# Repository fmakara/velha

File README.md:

# velha
Jogo da velha para o Mural do PET

Feito com KiCAD versão 4.0.2 e Atmel Studio

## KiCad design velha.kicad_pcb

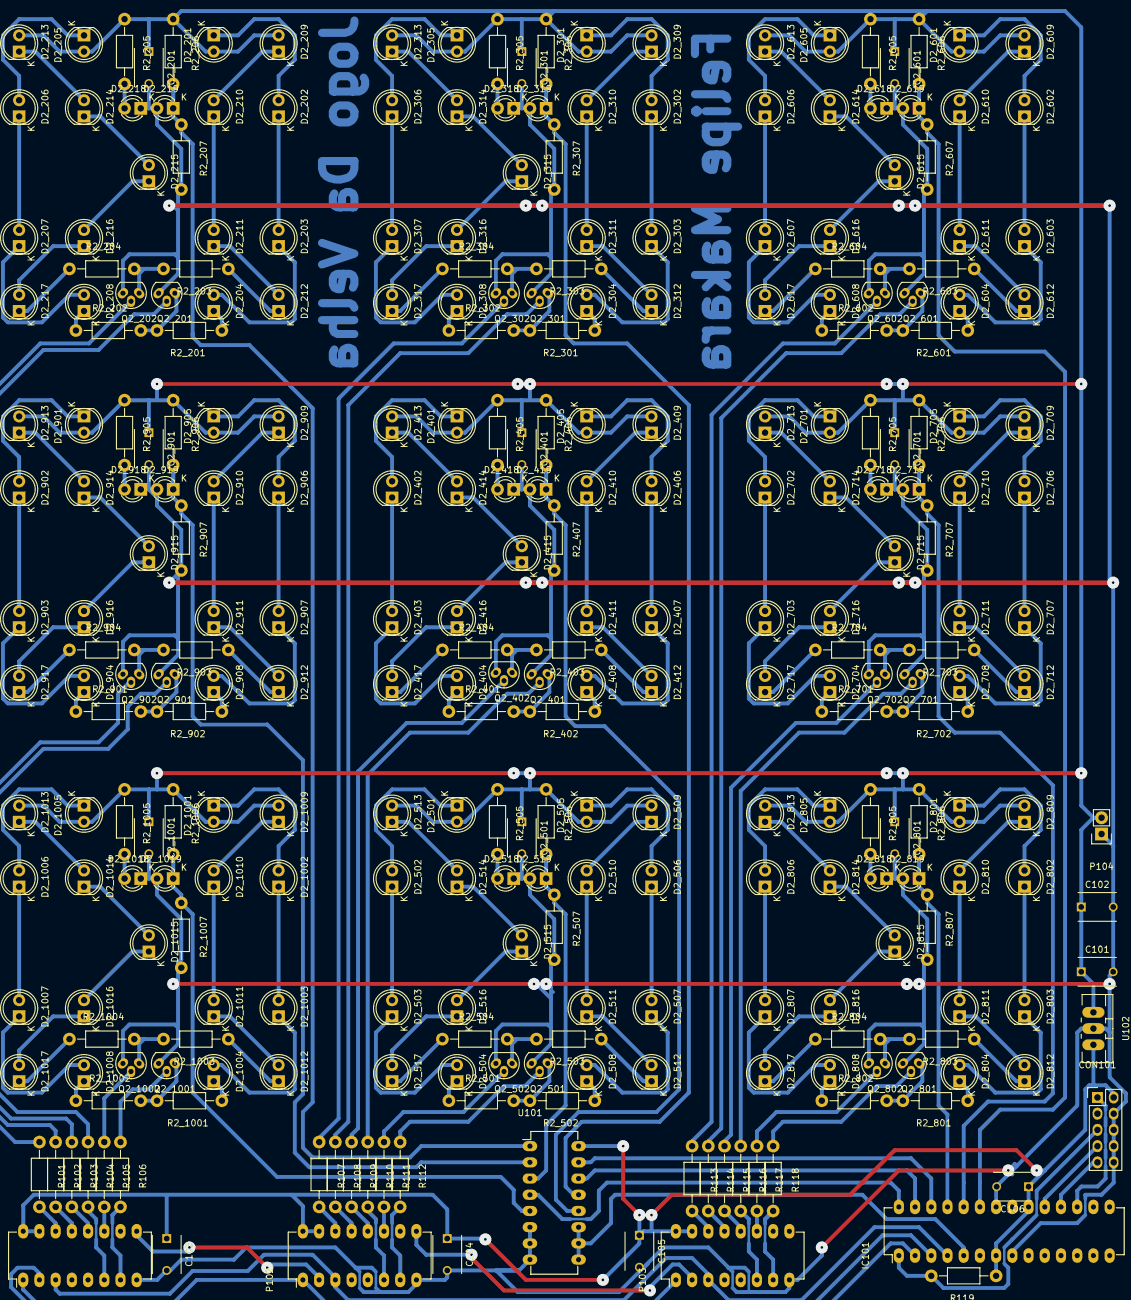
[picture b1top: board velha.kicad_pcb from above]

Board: 2 copper layers, 294 parts (0 on the bottom side), 241 nets.

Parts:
C2_201, C2_301, C2_401, C2_501, C2_601, C2_701, C2_801, C2_901, C2_1001, C102, C103, C104, C105, C106: 100n; C_Disc_D6_P5
C101: 100u; C_Disc_D6_P5
CON101: AVR-ISP-10; Pin_Header_Straight_2x05
D2_201, D2_202, D2_203, D2_204, D2_205, D2_206, D2_207, D2_208, D2_301, D2_302, D2_303, D2_304, D2_305, D2_306, D2_307, D2_308, D2_401, D2_402, D2_403, D2_404, D2_405, D2_406, D2_407, D2_408, D2_501, D2_502, D2_503, D2_504, D2_505, D2_506, D2_507, D2_508, D2_601, D2_602, D2_603, D2_604, D2_605, D2_606, D2_607, D2_608, D2_701, D2_702, D2_703, D2_704, D2_705, D2_706, D2_707, D2_708, D2_801, D2_802, D2_803, D2_804, D2_805, D2_806, D2_807, D2_808, D2_901, D2_902, D2_903, D2_904, D2_905, D2_906, D2_907, D2_908, D2_1001, D2_1002, D2_1003, D2_1004, D2_1005, D2_1006, D2_1007, D2_1008: G; LED-5MM
D2_209, D2_210, D2_211, D2_212, D2_213, D2_214, D2_215, D2_216, D2_217, D2_309, D2_310, D2_311, D2_312, D2_313, D2_314, D2_315, D2_316, D2_317, D2_409, D2_410, D2_411, D2_412, D2_413, D2_414, D2_415, D2_416, D2_417, D2_509, D2_510, D2_511, D2_512, D2_513, D2_514, D2_515, D2_516, D2_517, D2_609, D2_610, D2_611, D2_612, D2_613, D2_614, D2_615, D2_616, D2_617, D2_709, D2_710, D2_711, D2_712, D2_713, D2_714, D2_715, D2_716, D2_717, D2_809, D2_810, D2_811, D2_812, D2_813, D2_814, D2_815, D2_816, D2_817, D2_909, D2_910, D2_911, D2_912, D2_913, D2_914, D2_915, D2_916, D2_917, D2_1009, D2_1010, D2_1011, D2_1012, D2_1013, D2_1014, D2_1015, D2_1016, D2_1017: R; LED-5MM
D2_218, D2_318, D2_418, D2_518, D2_618, D2_718, D2_818, D2_918, D2_1018: LED; LED-3MM
D2_219, D2_319, D2_419, D2_519, D2_619, D2_719, D2_819, D2_919, D2_1019: PHOTO; LED-3MM
IC101: ATMEGA328P-P; DIP-28_W7.62mm_LongPads
P101, P102, P103: 4094; DIP-16_W7.62mm_LongPads
P104: CONN_01X02; Pin_Header_Straight_1x02
Q2_201, Q2_202, Q2_301, Q2_302, Q2_401, Q2_402, Q2_501, Q2_502, Q2_601, Q2_602, Q2_701, Q2_702, Q2_801, Q2_802, Q2_901, Q2_902, Q2_1001, Q2_1002: Q_NPN_CBE; TO-92_Molded_Narrow_Oval
R2_201, R2_202, R2_203, R2_301, R2_302, R2_303, R2_401, R2_402, R2_403, R2_501, R2_502, R2_503, R2_601, R2_602, R2_603, R2_701, R2_702, R2_703, R2_801, R2_802, R2_803, R2_901, R2_902, R2_903, R2_1001, R2_1002, R2_1003: 100r; Resistor_Horizontal_RM10mm
R2_204, R2_304, R2_404, R2_504, R2_604, R2_704, R2_804, R2_904, R2_1004: 50r; Resistor_Horizontal_RM10mm
R2_205, R2_305, R2_405, R2_505, R2_605, R2_705, R2_805, R2_905, R2_1005: 1k; Resistor_Horizontal_RM10mm
R2_206, R2_207, R2_306, R2_307, R2_406, R2_407, R2_506, R2_507, R2_606, R2_607, R2_706, R2_707, R2_806, R2_807, R2_906, R2_907, R2_1006, R2_1007, R119: 10k; Resistor_Horizontal_RM10mm
R101, R102, R103, R104, R105, R106, R107, R108, R109, R110, R111, R112, R113, R114, R115, R116, R117, R118: 500; Resistor_Horizontal_RM10mm
U101: 4053; DIP-16_W7.62mm_LongPads
U102: 7805; TO-220_Neutral123_Vertical_LargePads

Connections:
+5V: C103.1, C104.1, C105.1, C106.1, CON101.2, IC101.7, IC101.20, P101.15, P101.16, P102.15, P102.16, P103.15, P103.16, R119.1, U101.16
+12V: C2_201.1, C2_301.1, C2_401.1, C2_501.1, C2_601.1, C2_701.1, C2_801.1, C2_901.1, C2_1001.1, C101.1, C102.1, D2_201.2, D2_205.2, D2_209.2, D2_213.2, D2_301.2, D2_305.2, D2_309.2, D2_313.2, D2_401.2, D2_405.2, D2_409.2, D2_413.2, D2_501.2, D2_505.2, D2_509.2, D2_513.2, D2_601.2, D2_605.2, D2_609.2, D2_613.2, D2_701.2, D2_705.2, D2_709.2, D2_713.2, D2_801.2, D2_805.2, D2_809.2, D2_813.2, D2_901.2, D2_905.2, D2_909.2, D2_913.2, D2_1001.2, D2_1005.2, D2_1009.2, D2_1013.2, P104.2, R2_205.1, R2_206.1, R2_305.1, R2_306.1, R2_405.1, R2_406.1, R2_505.1, R2_506.1, R2_605.1, R2_606.1, R2_705.1, R2_706.1, R2_805.1, R2_806.1, R2_905.1, R2_906.1, R2_1005.1, R2_1006.1
/leds1/o: Q2_201.2, R102.1
/leds1/s: D2_219.1, R2_206.2, R2_207.1, U101.1
/leds1/x: Q2_202.2, R101.1
/leds2/o: Q2_301.2, R108.1
/leds2/s: D2_319.1, R2_306.2, R2_307.1, U101.13
/leds2/x: Q2_302.2, R107.1
/leds3/o: Q2_601.2, R114.1
/leds3/s: D2_619.1, IC101.23, R2_606.2, R2_607.1
/leds3/x: Q2_602.2, R113.1
/leds4/o: Q2_901.2, R104.1
/leds4/s: D2_919.1, R2_906.2, R2_907.1, U101.2
/leds4/x: Q2_902.2, R103.1
/leds5/o: Q2_401.2, R110.1
/leds5/s: D2_419.1, R2_406.2, R2_407.1, U101.12
/leds5/x: Q2_402.2, R109.1
/leds6/o: Q2_701.2, R116.1
/leds6/s: D2_719.1, IC101.24, R2_706.2, R2_707.1
/leds6/x: Q2_702.2, R115.1
/leds7/o: Q2_1001.2, R106.1
/leds7/s: D2_1019.1, R2_1006.2, R2_1007.1, U101.5
/leds7/x: Q2_1002.2, R105.1
/leds8/o: Q2_501.2, R112.1
/leds8/s: D2_519.1, R2_506.2, R2_507.1, U101.3
/leds8/x: Q2_502.2, R111.1
/leds9/o: Q2_801.2, R118.1
/leds9/s: D2_819.1, IC101.25, R2_806.2, R2_807.1
/leds9/x: Q2_802.2, R117.1
GND: C2_201.2, C2_301.2, C2_401.2, C2_501.2, C2_601.2, C2_701.2, C2_801.2, C2_901.2, C2_1001.2, C101.2, C102.2, C103.2, C104.2, C105.2, C106.2, CON101.4, CON101.6, CON101.8, CON101.10, D2_218.1, D2_219.2, D2_318.1, D2_319.2, D2_418.1, D2_419.2, D2_518.1, D2_519.2, D2_618.1, D2_619.2, D2_718.1, D2_719.2, D2_818.1, D2_819.2, D2_918.1, D2_919.2, D2_1018.1, D2_1019.2, IC101.8, IC101.22, P101.8, P102.8, P103.8, P104.1, Q2_201.3, Q2_202.3, Q2_301.3, Q2_302.3, Q2_401.3, Q2_402.3, Q2_501.3, Q2_502.3, Q2_601.3, Q2_602.3, Q2_701.3, Q2_702.3, Q2_801.3, Q2_802.3, Q2_901.3, Q2_902.3, Q2_1001.3, Q2_1002.3, R2_207.2, R2_307.2, R2_407.2, R2_507.2, R2_607.2, R2_707.2, R2_807.2, R2_907.2, R2_1007.2, U101.6, U101.7, U101.8
unnamed: CON101.1, IC101.17
unnamed: CON101.5, IC101.1, R119.2
unnamed: CON101.7, IC101.19
unnamed: CON101.9, IC101.18
unnamed: D2_201.1, D2_202.2
unnamed: D2_202.1, D2_203.2
unnamed: D2_203.1, D2_204.2
unnamed: D2_204.1, R2_201.1
unnamed: D2_205.1, D2_206.2
unnamed: D2_206.1, D2_207.2
unnamed: D2_207.1, D2_208.2
unnamed: D2_208.1, R2_202.1
unnamed: D2_209.1, D2_210.2
unnamed: D2_210.1, D2_211.2
unnamed: D2_211.1, D2_212.2
unnamed: D2_212.1, R2_203.1
unnamed: D2_213.1, D2_214.2
unnamed: D2_214.1, D2_215.2
unnamed: D2_215.1, D2_216.2
unnamed: D2_216.1, D2_217.2
unnamed: D2_217.1, R2_204.1
unnamed: D2_218.2, R2_205.2
unnamed: D2_301.1, D2_302.2
unnamed: D2_302.1, D2_303.2
unnamed: D2_303.1, D2_304.2
unnamed: D2_304.1, R2_301.1
unnamed: D2_305.1, D2_306.2
unnamed: D2_306.1, D2_307.2
unnamed: D2_307.1, D2_308.2
unnamed: D2_308.1, R2_302.1
unnamed: D2_309.1, D2_310.2
unnamed: D2_310.1, D2_311.2
unnamed: D2_311.1, D2_312.2
unnamed: D2_312.1, R2_303.1
unnamed: D2_313.1, D2_314.2
unnamed: D2_314.1, D2_315.2
unnamed: D2_315.1, D2_316.2
unnamed: D2_316.1, D2_317.2
unnamed: D2_317.1, R2_304.1
unnamed: D2_318.2, R2_305.2
unnamed: D2_401.1, D2_402.2
unnamed: D2_402.1, D2_403.2
unnamed: D2_403.1, D2_404.2
unnamed: D2_404.1, R2_401.1
unnamed: D2_405.1, D2_406.2
unnamed: D2_406.1, D2_407.2
unnamed: D2_407.1, D2_408.2
unnamed: D2_408.1, R2_402.1
unnamed: D2_409.1, D2_410.2
unnamed: D2_410.1, D2_411.2
unnamed: D2_411.1, D2_412.2
unnamed: D2_412.1, R2_403.1
unnamed: D2_413.1, D2_414.2
unnamed: D2_414.1, D2_415.2
unnamed: D2_415.1, D2_416.2
unnamed: D2_416.1, D2_417.2
unnamed: D2_417.1, R2_404.1
unnamed: D2_418.2, R2_405.2
unnamed: D2_501.1, D2_502.2
unnamed: D2_502.1, D2_503.2
unnamed: D2_503.1, D2_504.2
unnamed: D2_504.1, R2_501.1
unnamed: D2_505.1, D2_506.2
unnamed: D2_506.1, D2_507.2
unnamed: D2_507.1, D2_508.2
unnamed: D2_508.1, R2_502.1
unnamed: D2_509.1, D2_510.2
unnamed: D2_510.1, D2_511.2
unnamed: D2_511.1, D2_512.2
unnamed: D2_512.1, R2_503.1
unnamed: D2_513.1, D2_514.2
unnamed: D2_514.1, D2_515.2
unnamed: D2_515.1, D2_516.2
unnamed: D2_516.1, D2_517.2
unnamed: D2_517.1, R2_504.1
unnamed: D2_518.2, R2_505.2
unnamed: D2_601.1, D2_602.2
unnamed: D2_602.1, D2_603.2
unnamed: D2_603.1, D2_604.2
unnamed: D2_604.1, R2_601.1
unnamed: D2_605.1, D2_606.2
unnamed: D2_606.1, D2_607.2
unnamed: D2_607.1, D2_608.2
unnamed: D2_608.1, R2_602.1
unnamed: D2_609.1, D2_610.2
unnamed: D2_610.1, D2_611.2
unnamed: D2_611.1, D2_612.2
unnamed: D2_612.1, R2_603.1
unnamed: D2_613.1, D2_614.2
unnamed: D2_614.1, D2_615.2
unnamed: D2_615.1, D2_616.2
unnamed: D2_616.1, D2_617.2
unnamed: D2_617.1, R2_604.1
unnamed: D2_618.2, R2_605.2
unnamed: D2_701.1, D2_702.2
unnamed: D2_702.1, D2_703.2
unnamed: D2_703.1, D2_704.2
unnamed: D2_704.1, R2_701.1
unnamed: D2_705.1, D2_706.2
unnamed: D2_706.1, D2_707.2
unnamed: D2_707.1, D2_708.2
unnamed: D2_708.1, R2_702.1
unnamed: D2_709.1, D2_710.2
unnamed: D2_710.1, D2_711.2
unnamed: D2_711.1, D2_712.2
unnamed: D2_712.1, R2_703.1
unnamed: D2_713.1, D2_714.2
unnamed: D2_714.1, D2_715.2
unnamed: D2_715.1, D2_716.2
unnamed: D2_716.1, D2_717.2
unnamed: D2_717.1, R2_704.1
unnamed: D2_718.2, R2_705.2
unnamed: D2_801.1, D2_802.2
unnamed: D2_802.1, D2_803.2
unnamed: D2_803.1, D2_804.2
unnamed: D2_804.1, R2_801.1
unnamed: D2_805.1, D2_806.2
unnamed: D2_806.1, D2_807.2
unnamed: D2_807.1, D2_808.2
unnamed: D2_808.1, R2_802.1
unnamed: D2_809.1, D2_810.2
unnamed: D2_810.1, D2_811.2
unnamed: D2_811.1, D2_812.2
unnamed: D2_812.1, R2_803.1
unnamed: D2_813.1, D2_814.2
unnamed: D2_814.1, D2_815.2
unnamed: D2_815.1, D2_816.2
unnamed: D2_816.1, D2_817.2
unnamed: D2_817.1, R2_804.1
unnamed: D2_818.2, R2_805.2
unnamed: D2_901.1, D2_902.2
unnamed: D2_902.1, D2_903.2
unnamed: D2_903.1, D2_904.2
unnamed: D2_904.1, R2_901.1
unnamed: D2_905.1, D2_906.2
unnamed: D2_906.1, D2_907.2
unnamed: D2_907.1, D2_908.2
unnamed: D2_908.1, R2_902.1
unnamed: D2_909.1, D2_910.2
unnamed: D2_910.1, D2_911.2
unnamed: D2_911.1, D2_912.2
unnamed: D2_912.1, R2_903.1
unnamed: D2_913.1, D2_914.2
unnamed: D2_914.1, D2_915.2
unnamed: D2_915.1, D2_916.2
unnamed: D2_916.1, D2_917.2
unnamed: D2_917.1, R2_904.1
unnamed: D2_918.2, R2_905.2
unnamed: D2_1001.1, D2_1002.2
unnamed: D2_1002.1, D2_1003.2
unnamed: D2_1003.1, D2_1004.2
unnamed: D2_1004.1, R2_1001.1
unnamed: D2_1005.1, D2_1006.2
unnamed: D2_1006.1, D2_1007.2
unnamed: D2_1007.1, D2_1008.2
unnamed: D2_1008.1, R2_1002.1
unnamed: D2_1009.1, D2_1010.2
unnamed: D2_1010.1, D2_1011.2
unnamed: D2_1011.1, D2_1012.2
unnamed: D2_1012.1, R2_1003.1
unnamed: D2_1013.1, D2_1014.2
unnamed: D2_1014.1, D2_1015.2
unnamed: D2_1015.1, D2_1016.2
unnamed: D2_1016.1, D2_1017.2
unnamed: D2_1017.1, R2_1004.1
unnamed: D2_1018.2, R2_1005.2
unnamed: IC101.2, P101.2
unnamed: IC101.3, P101.1, P102.1, P103.1
unnamed: IC101.4, P101.3, P102.3, P103.3
unnamed: IC101.5, U101.9, U101.10, U101.11
unnamed: IC101.26, U101.15
unnamed: IC101.27, U101.14
unnamed: IC101.28, U101.4
unnamed: P101.6, R104.2
unnamed: P101.7, R106.2
unnamed: P101.9, P102.2
unnamed: P101.11, R105.2
unnamed: P101.12, R103.2
unnamed: P101.13, R102.2
unnamed: P101.14, R101.2
unnamed: P102.6, R110.2
unnamed: P102.7, R112.2
unnamed: P102.9, P103.2
unnamed: P102.11, R111.2
unnamed: P102.12, R109.2
unnamed: P102.13, R108.2
unnamed: P102.14, R107.2
unnamed: P103.6, R116.2
unnamed: P103.7, R118.2
unnamed: P103.11, R117.2
unnamed: P103.12, R115.2
unnamed: P103.13, R114.2
unnamed: P103.14, R113.2
unnamed: Q2_201.1, R2_201.2, R2_202.2
unnamed: Q2_202.1, R2_203.2, R2_204.2
unnamed: Q2_301.1, R2_301.2, R2_302.2
unnamed: Q2_302.1, R2_303.2, R2_304.2
unnamed: Q2_401.1, R2_401.2, R2_402.2
unnamed: Q2_402.1, R2_403.2, R2_404.2
unnamed: Q2_501.1, R2_501.2, R2_502.2
unnamed: Q2_502.1, R2_503.2, R2_504.2
unnamed: Q2_601.1, R2_601.2, R2_602.2
unnamed: Q2_602.1, R2_603.2, R2_604.2
unnamed: Q2_701.1, R2_701.2, R2_702.2
unnamed: Q2_702.1, R2_703.2, R2_704.2
unnamed: Q2_801.1, R2_801.2, R2_802.2
unnamed: Q2_802.1, R2_803.2, R2_804.2
unnamed: Q2_901.1, R2_901.2, R2_902.2
unnamed: Q2_902.1, R2_903.2, R2_904.2
unnamed: Q2_1001.1, R2_1001.2, R2_1002.2
unnamed: Q2_1002.1, R2_1003.2, R2_1004.2

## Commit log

2016-06-08 Projeto Completo
